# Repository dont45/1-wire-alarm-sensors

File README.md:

# 1-wire-alarm-sensors
Collection of 1-wire sensor devices

A switch 'closure' sensor such as a typical magnetic reed switch is connected to the photonAlarm 
by use of a 1-wire device such as a ds2406 or ds2413.  These devices provide two gpio 'pins' controlled
by 1-wire commands from the photonAlarm.  The gpio pins are generally labled PIO pins, PIO-A and PIO-B
for the two devices mentioned.  These are bi-directional open drain pins which can serve to detect a 
switch closure or drive a device for output.  The advantage of this design is that a single wire (and a ground)
connects all the alarm sensors, with the 1-wire devices being connected in a varity of topologies, i.e. star,
multi-drop, or straight line.

Since in the simplest configuration there is no voltage supplied to the sensor, just the 1-wire data line,
there is no voltage to detect by the sensor switch closing.  In order to keep the sensor network in the
spirit of 1-wire, a method, called parasitic power, can be used to power the detection circuit of the
reed switch.  This method is implemented by a parasitic charge circuit which taps the 1-wire data line
to keep a capacitor charged.  The charge on this capacitor is used to drive the voltage detection at the
device's PIO port.  This design is attached as sensor-2406p+.  Included are Eagle files as well as the .pdf's.

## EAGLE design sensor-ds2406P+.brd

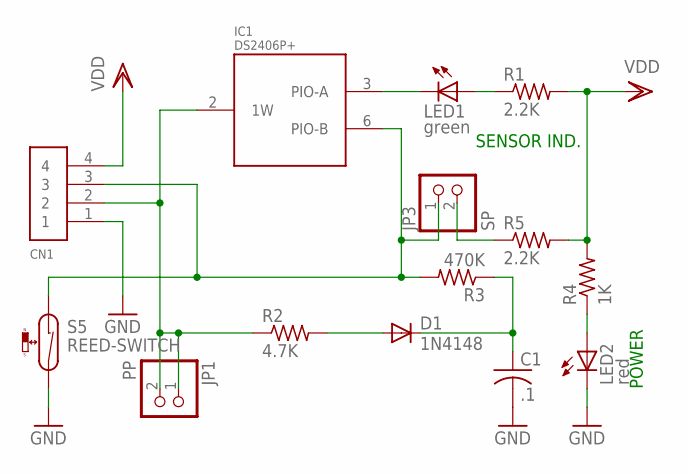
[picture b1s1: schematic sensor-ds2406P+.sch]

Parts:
C1: .1; C0805K
CN1: 1X4-BIG; 1X04-BIG
D1: 1N4148; SOT23
IC1: DS2406P+; SO06
JP1: PP; 1X02
JP3: SP; 1X02
LED1: green; LED3MM
LED2: red; LED3MM
R1, R5: 2.2K; R0805
R2: 4.7K; R0805
R3: 470K; R0805
R4: 1K; R0805
S5: REED-SWITCH; MK15

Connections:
GND: C1.2, CN1.1, IC1.1 (GND), LED2.K (C), S5.2
IO: CN1.2, IC1.2 (1W), JP1.1, JP1.2, R2.1
unnamed: LED1.A, R1.1
unnamed: D1.1 (A), R2.2
unnamed: C1.1, D1.3 (C), R3.1
unnamed: LED2.A, R4.1
unnamed: JP3.2, R5.1
PIO$A: IC1.3 (PIO-A), LED1.K (C)
PIO$B: CN1.3, IC1.6 (PIO-B), JP3.1, R3.2, S5.1
VDD: CN1.4, IC1.4 (VDD), R1.2, R4.2, R5.2

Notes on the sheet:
SENSOR IND.
POWER

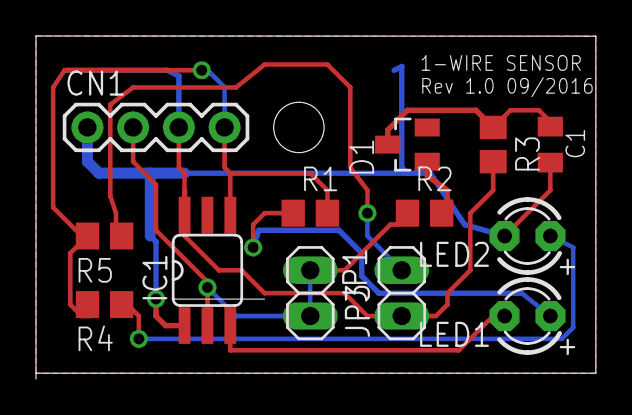
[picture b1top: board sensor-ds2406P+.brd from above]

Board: 2 copper layers, 31.1 x 19.1 mm, 14 parts (1 on the bottom side), 10 nets.
